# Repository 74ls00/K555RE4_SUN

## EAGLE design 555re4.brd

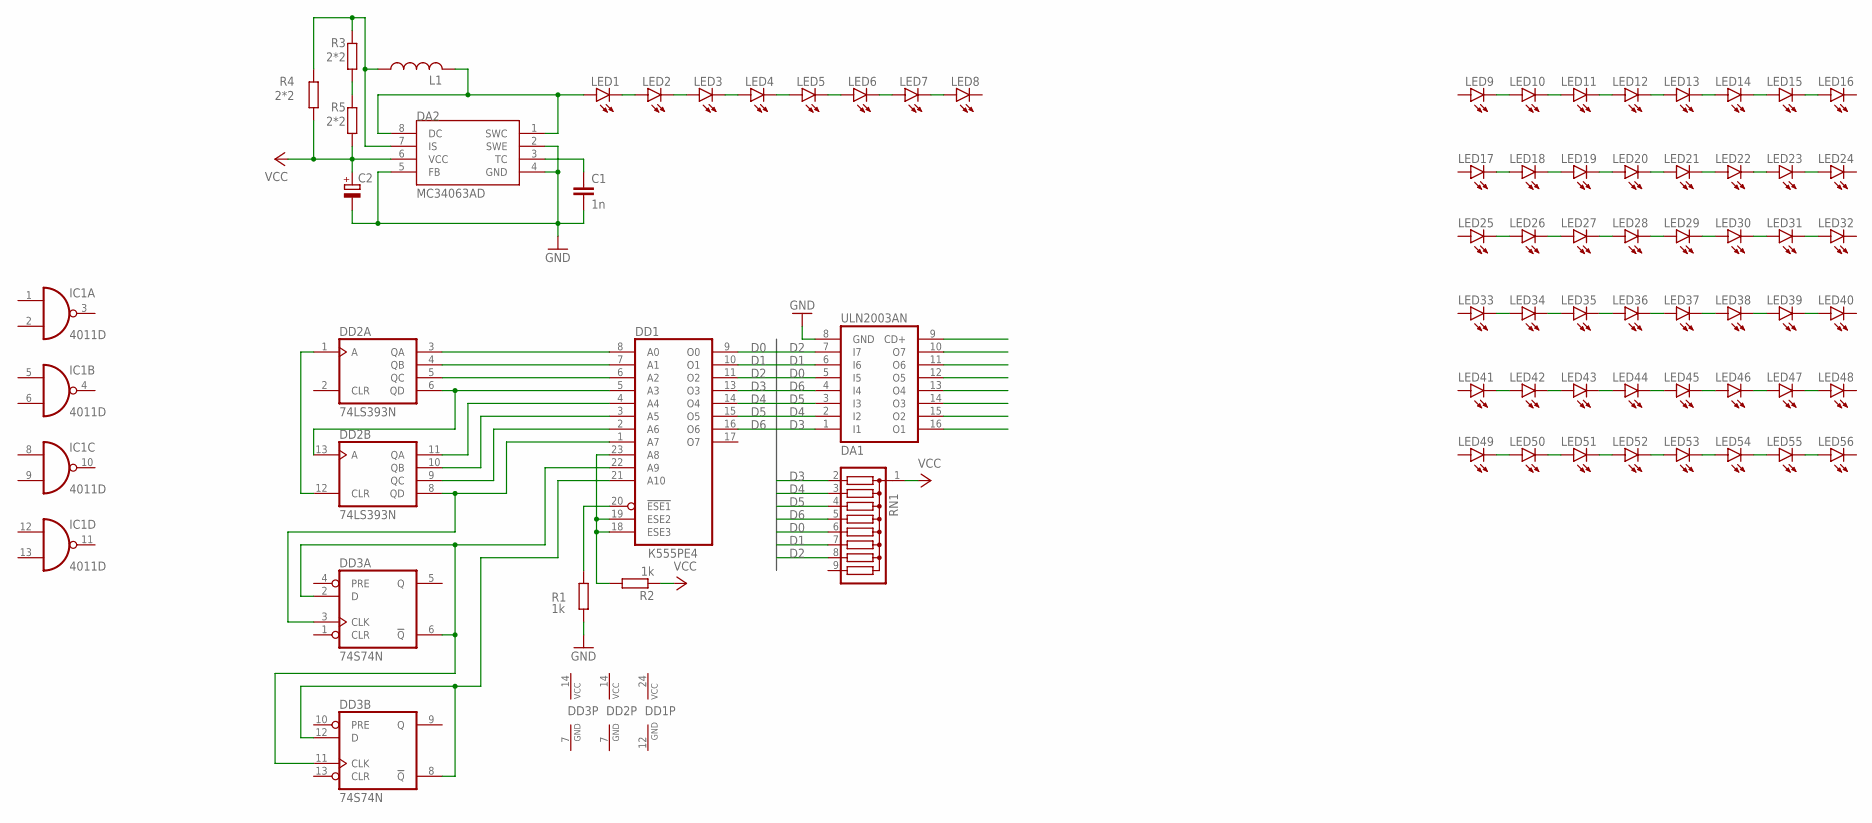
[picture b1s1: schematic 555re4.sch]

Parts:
C1: 1n; C050-025X075
C2: CPOL-EUE2-5; E2-5
DA1: ULN2003AN; DIL16
DA2: MC34063AD; SOIC8
DD1: K555RE4; 239.24-2
DD2: 74LS393N; DIL14
DD3: 74S74N; DIL14
IC1: 4011D; SO14
L1: L-USTJ3-U2; TJ3-U2
LED1, LED2, LED3, LED4, LED5, LED6, LED7, LED8, LED9, LED10, LED11, LED12, LED13, LED14, LED15, LED16, LED17, LED18, LED19, LED20, LED21, LED22, LED23, LED24, LED25, LED27, LED28, LED29, LED30, LED31, LED32, LED33, LED34, LED35, LED36, LED37, LED38, LED39, LED40, LED41, LED42, LED43, LED44, LED45, LED46, LED47, LED48, LED49, LED50, LED51, LED52, LED53, LED54, LED55, LED56: LED3MM
LED26: LED-3MM-NO_SILK; LED3MM-NS
R1, R2: 1k; 0207/10
R3, R4, R5: 2*2; M0805
RN1: G08R; SIL9

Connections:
D0: DA1.5 (I5), DD1.9 (O0), RN1.6
D1: DA1.6 (I6), DD1.10 (O1), RN1.7
D2: DA1.7 (I7), DD1.11 (O2), RN1.8
D3: DA1.1 (I1), DD1.13 (O3), RN1.2
D4: DA1.2 (I2), DD1.14 (O4), RN1.3
D5: DA1.3 (I3), DD1.15 (O5), RN1.4
D6: DA1.4 (I4), DD1.16 (O6), RN1.5
GND: C1.2, C2.-, DA1.8 (GND), DA2.2 (SWE), DA2.4 (GND), DA2.5 (FB), DD1.12 (GND), DD2.7 (GND), DD3.7 (GND), R1.2
unnamed: DD2.1 (A), DD2.12 (CLR)
unnamed: DD1.22 (A9), DD3.2 (D), DD3.6 (!Q), DD3.11 (CLK)
unnamed: DD1.8 (A0), DD2.3 (QA)
unnamed: DD1.7 (A1), DD2.4 (QB)
unnamed: DD1.6 (A2), DD2.5 (QC)
unnamed: DD1.4 (A4), DD2.11 (QA)
unnamed: DD1.3 (A5), DD2.10 (QB)
unnamed: DD1.2 (A6), DD2.9 (QC)
unnamed: DD1.1 (A7), DD2.8 (QD), DD3.3 (CLK)
unnamed: DD1.5 (A3), DD2.6 (QD), DD2.13 (A)
unnamed: DD1.21 (A10), DD3.8 (!Q), DD3.12 (D)
unnamed: LED1.K (C), LED2.A
unnamed: DA2.1 (SWC), DA2.8 (DC), L1.2, LED1.A
unnamed: LED2.K (C), LED3.A
unnamed: DA2.7 (IS), L1.1, R3.2, R4.2
unnamed: LED17.K (C), LED18.A
unnamed: DD1.18 (ESE3), DD1.19 (ESE2), DD1.23 (A8), R2.2
unnamed: C1.1, DA2.3 (TC)
unnamed: DD1.20 (!ESE1), R1.1
unnamed: LED4.K (C), LED5.A
unnamed: LED5.K (C), LED6.A
unnamed: LED3.K (C), LED4.A
unnamed: LED6.K (C), LED7.A
unnamed: LED7.K (C), LED8.A
unnamed: LED9.K (C), LED10.A
unnamed: LED10.K (C), LED11.A
unnamed: LED12.K (C), LED13.A
unnamed: LED13.K (C), LED14.A
unnamed: LED11.K (C), LED12.A
unnamed: LED14.K (C), LED15.A
unnamed: LED15.K (C), LED16.A
unnamed: LED18.K (C), LED19.A
unnamed: LED20.K (C), LED21.A
unnamed: LED21.K (C), LED22.A
unnamed: LED19.K (C), LED20.A
unnamed: LED22.K (C), LED23.A
unnamed: LED23.K (C), LED24.A
unnamed: LED25.K (C), LED26.A
unnamed: LED26.K (C), LED27.A
unnamed: LED28.K (C), LED29.A
unnamed: LED29.K (C), LED30.A
unnamed: LED27.K (C), LED28.A
unnamed: LED30.K (C), LED31.A
unnamed: LED31.K (C), LED32.A
unnamed: LED33.K (C), LED34.A
unnamed: LED34.K (C), LED35.A
unnamed: LED36.K (C), LED37.A
unnamed: LED37.K (C), LED38.A
unnamed: LED35.K (C), LED36.A
unnamed: LED38.K (C), LED39.A
unnamed: LED39.K (C), LED40.A
unnamed: LED41.K (C), LED42.A
unnamed: LED42.K (C), LED43.A
unnamed: LED44.K (C), LED45.A
unnamed: LED45.K (C), LED46.A
unnamed: LED43.K (C), LED44.A
unnamed: LED46.K (C), LED47.A
unnamed: LED47.K (C), LED48.A
unnamed: LED49.K (C), LED50.A
unnamed: LED50.K (C), LED51.A
unnamed: LED52.K (C), LED53.A
unnamed: LED53.K (C), LED54.A
unnamed: LED51.K (C), LED52.A
unnamed: LED54.K (C), LED55.A
unnamed: LED55.K (C), LED56.A
unnamed: R3.1, R5.2
VCC: C2.+, DA2.6 (VCC), DD1.24 (VCC), DD2.14 (VCC), DD3.14 (VCC), R2.1, R4.1, R5.1, RN1.1
VDD: IC1.14 (VDD)
VSS: IC1.7 (VSS)

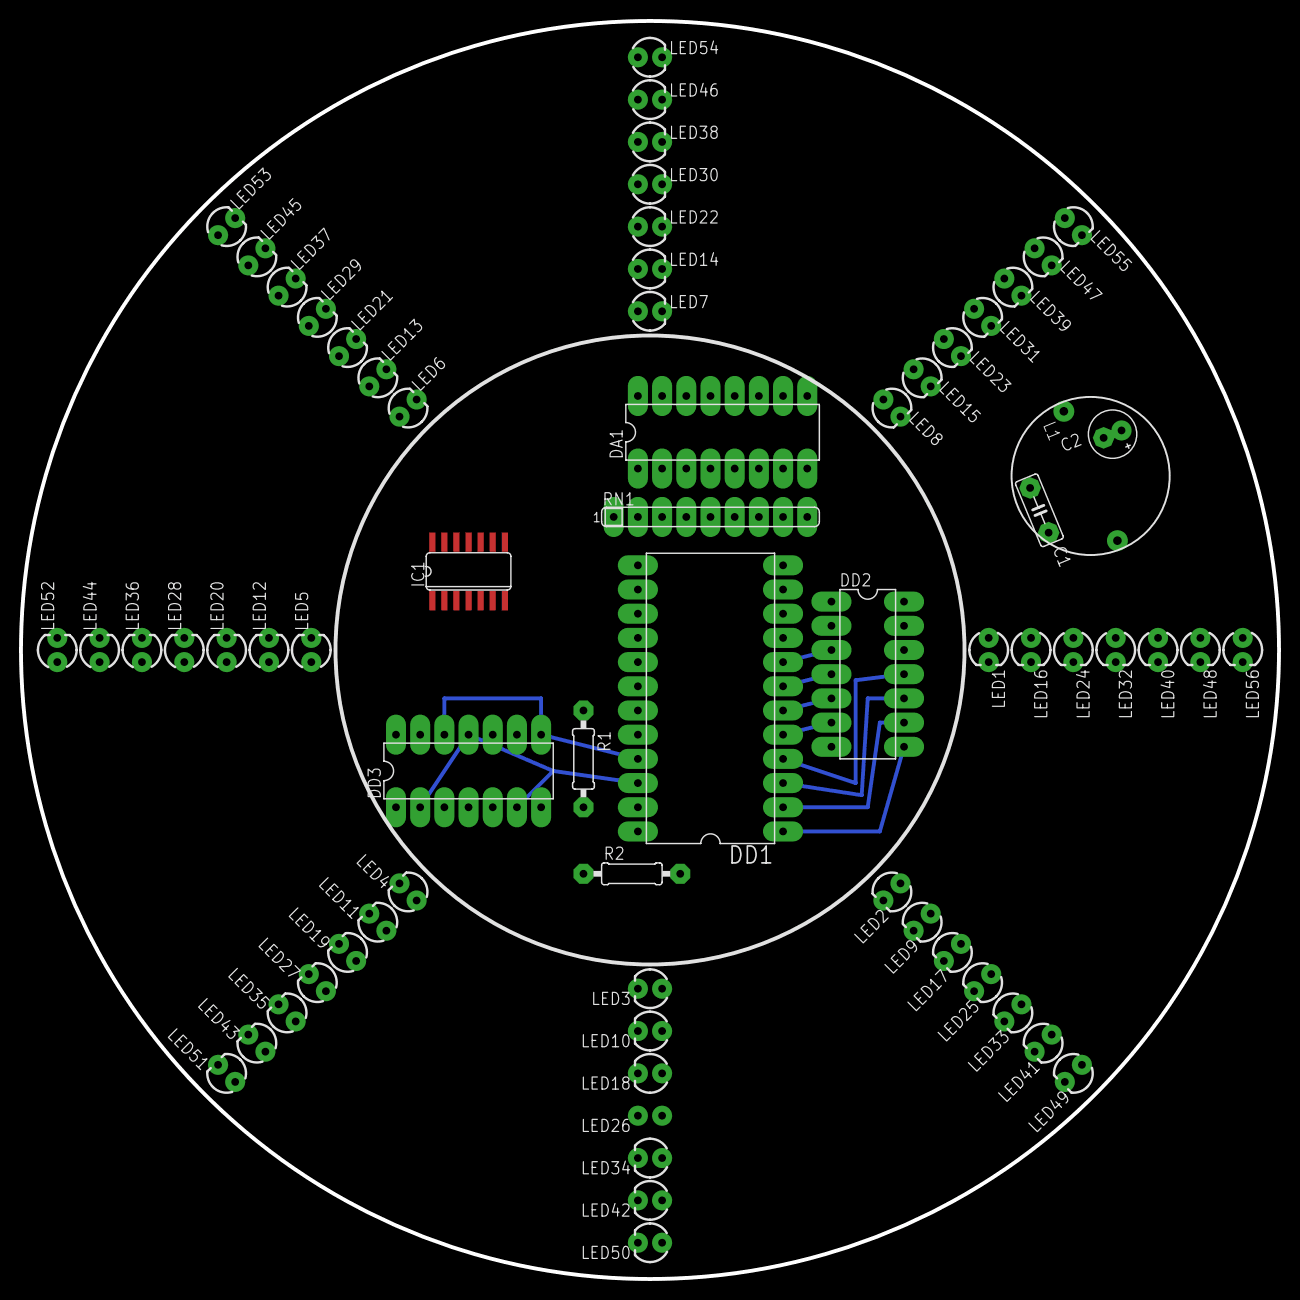
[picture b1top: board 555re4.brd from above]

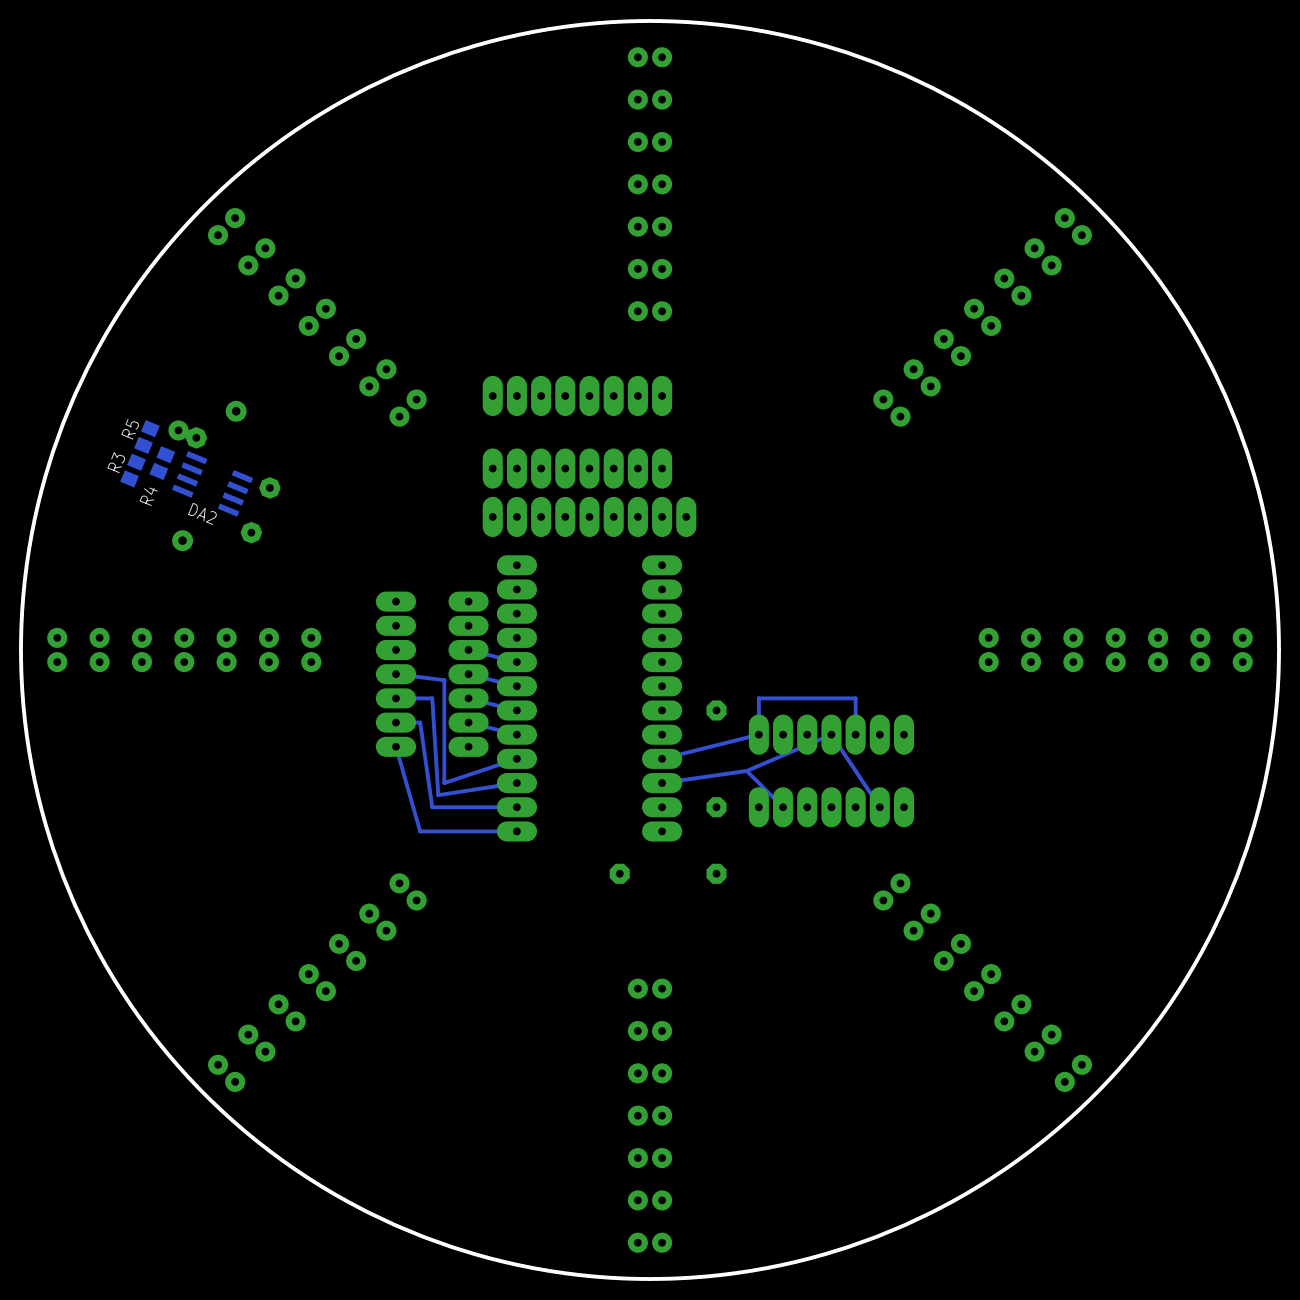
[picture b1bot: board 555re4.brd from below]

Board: 2 copper layers, 132.1 x 132.1 mm, 71 parts (4 on the bottom side), 75 nets.

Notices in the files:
parts and their libraries:
SparkFun-LED: Licensing: Creative Commons ShareAlike 4.0 International - https://creativecommons.org/licenses/by-sa/4.0
